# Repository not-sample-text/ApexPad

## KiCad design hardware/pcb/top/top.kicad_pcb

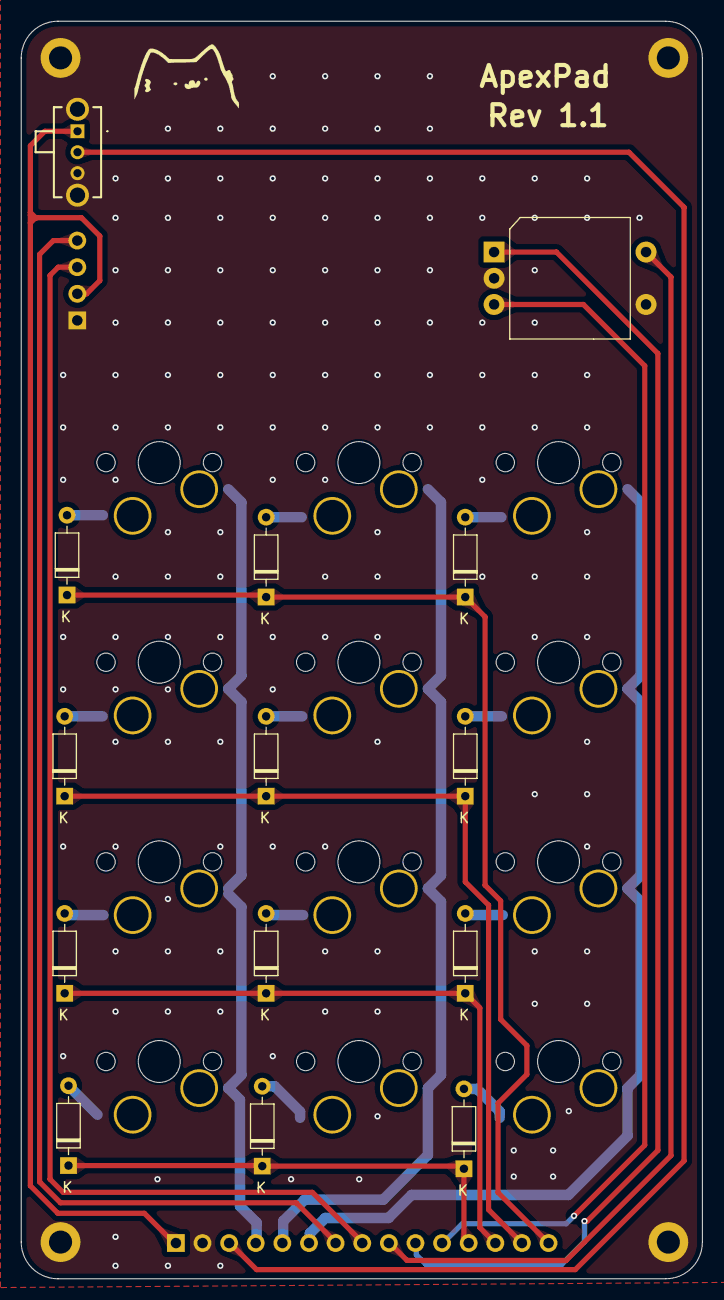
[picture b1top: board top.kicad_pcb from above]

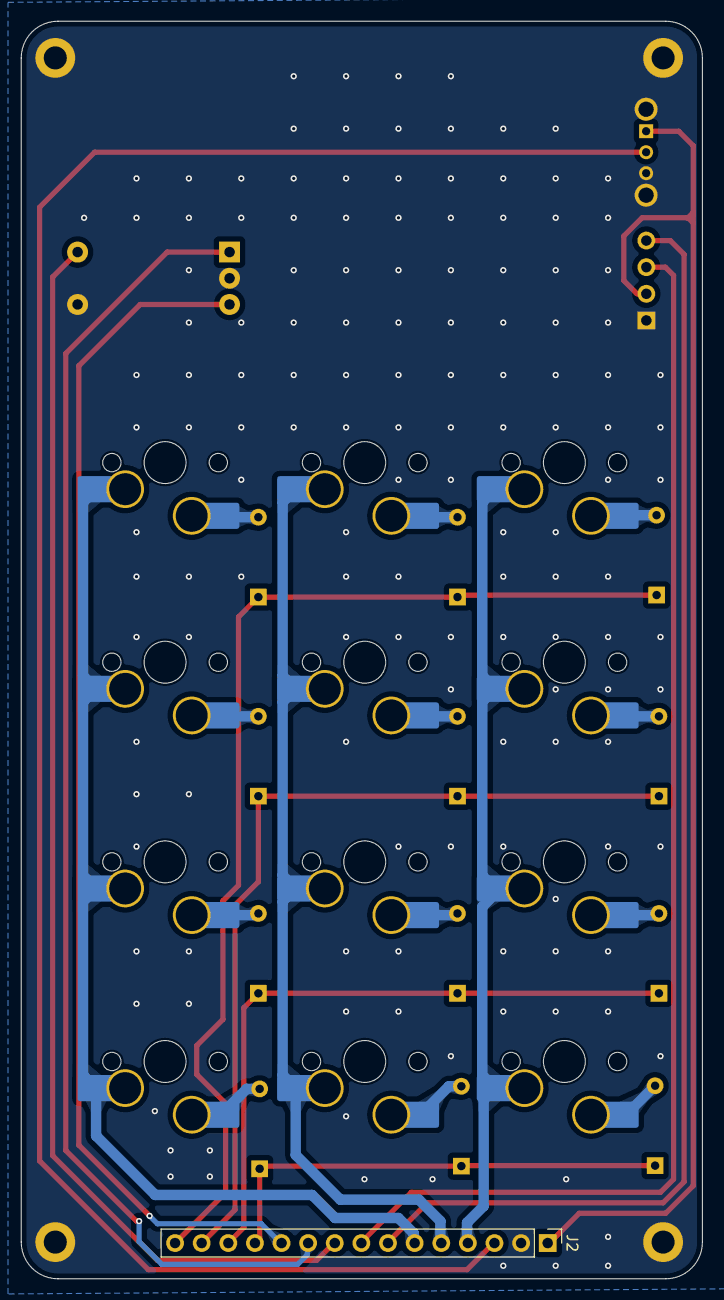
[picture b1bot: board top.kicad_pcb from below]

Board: 2 copper layers, 65.0 x 120.0 mm, 32 parts (13 on the bottom side), 27 nets.

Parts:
D1, D2, D3, D4, D5, D6, D7, D8, D9, D10, D11, D12: 1N4148; D_DO-35_SOD27_P7.62mm_Horizontal
H1, H2, H3, H4: MountingHole_Pad; MountingHole_2.2mm_M2_DIN965_Pad
J1: OLED_128x32
J2: Conn_01x15; PinHeader_1x15_P2.54mm_Vertical
S1, S2, S3, S4, S5, S6, S7, S8, S9, S10, S11, S12: Keyswitch; MX_Hotswap_1.00u
SW1: SLW-864574-5A-RA-N-D; SLW8645745ARAND
SW2: RotaryEncoder_Switch; Encoder_EC11_MX

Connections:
+3.3V: J1.2 (VCC), J2.1, SW1.1
BT_SELECT: J2.3, SW1.2
COL0: J2.4, S1.1, S4.1, S7.1, S10.1
COL1: J2.5, S2.1, S5.1, S8.1, S11.1
COL2: J2.6, S3.1, S6.1, S9.1, S12.1
ENC_CLK: J2.10, SW2.A
ENC_DT: J2.11, SW2.B
ENC_SW: J2.9, SW2.S2
GND: H1.1, H2.1, H3.1, H4.1, J1.1 (GND), J2.2, SW1.3, SW1.4 (MH1), SW1.5 (MH2), SW2.C, SW2.S1
unnamed: D1.2 (A), S1.2
unnamed: D2.2 (A), S2.2
unnamed: D3.2 (A), S3.2
unnamed: D4.2 (A), S4.2
unnamed: D5.2 (A), S5.2
unnamed: D6.2 (A), S6.2
unnamed: D7.2 (A), S7.2
unnamed: D8.2 (A), S8.2
unnamed: D9.2 (A), S9.2
unnamed: D10.2 (A), S10.2
unnamed: D11.2 (A), S11.2
unnamed: D12.2 (A), S12.2
OLED_SCL: J1.3 (SCL), J2.8
OLED_SDA: J1.4 (SDA), J2.7
ROW0: D1.1 (K), D2.1 (K), D3.1 (K), J2.15
ROW1: D4.1 (K), D5.1 (K), D6.1 (K), J2.14
ROW2: D7.1 (K), D8.1 (K), D9.1 (K), J2.13
ROW3: D10.1 (K), D11.1 (K), D12.1 (K), J2.12

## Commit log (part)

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2026-06-29 fixed grounding vias cutting column pads and updated name and rev number
